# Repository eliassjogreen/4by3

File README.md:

<br/>

A 12 key mechanical keypad that can be used as a arrow-pad, function-pad, numpad or whatever else you can imagine that fits onto 12  keys.

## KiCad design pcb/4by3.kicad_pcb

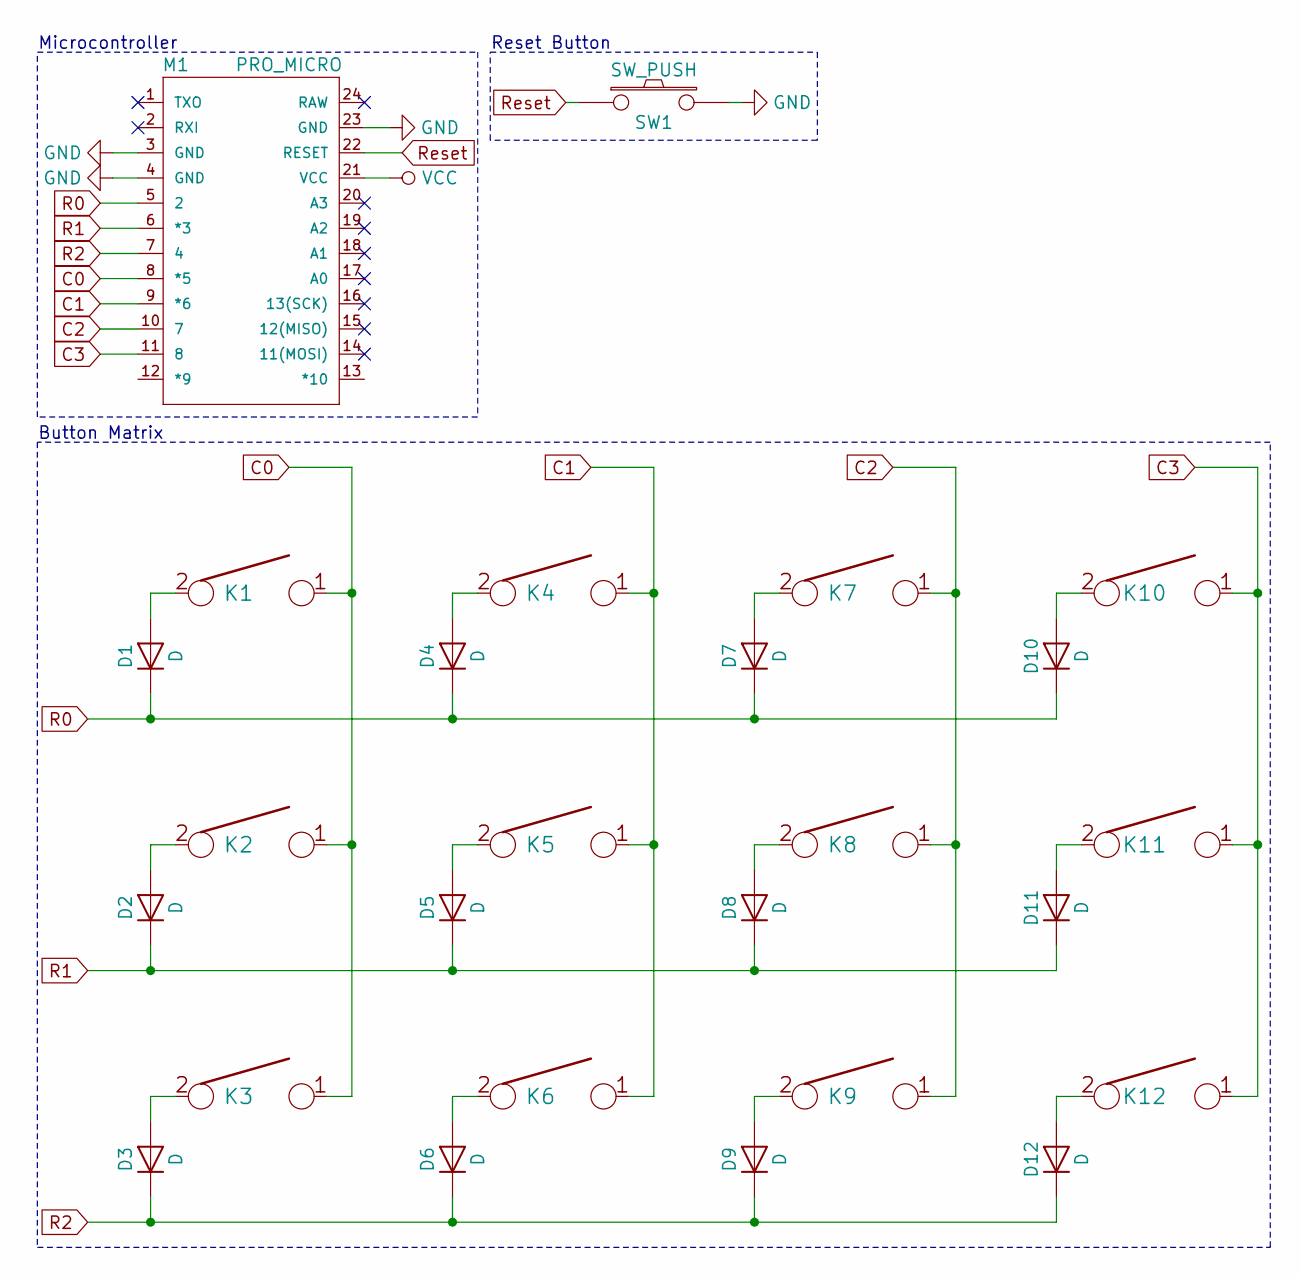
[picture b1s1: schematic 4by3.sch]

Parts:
D1, D2, D3, D4, D5, D6, D7, D8, D9, D10, D11, D12: D; DIODE
K1, K2, K3, K4, K5, K6, K7, K8, K9, K10, K11, K12: KEYSW; CHERRY_MX_PCB
M1: PRO_MICRO
SW1: SW_PUSH; RESET_BUTTON

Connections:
C0: K1.1, K2.1, K3.1, M1.8 (*5)
C1: K4.1, K5.1, K6.1, M1.9 (*6)
C2: K7.1, K8.1, K9.1, M1.10 (7)
C3: K10.1, K11.1, K12.1, M1.11 (8)
GND: M1.3 (GND), M1.4 (GND), M1.23 (GND), SW1.2
unnamed: D1.2 (A), K1.2
unnamed: D2.2 (A), K2.2
unnamed: D3.2 (A), K3.2
unnamed: D4.2 (A), K4.2
unnamed: D5.2 (A), K5.2
unnamed: D6.2 (A), K6.2
unnamed: D7.2 (A), K7.2
unnamed: D8.2 (A), K8.2
unnamed: D9.2 (A), K9.2
unnamed: D10.2 (A), K10.2
unnamed: D11.2 (A), K11.2
unnamed: D12.2 (A), K12.2
R0: D1.1 (K), D4.1 (K), D7.1 (K), D10.1 (K), M1.5 (2)
R1: D2.1 (K), D5.1 (K), D8.1 (K), D11.1 (K), M1.6 (*3)
R2: D3.1 (K), D6.1 (K), D9.1 (K), D12.1 (K), M1.7 (4)
Reset: M1.22 (RESET), SW1.1

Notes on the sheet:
Microcontroller
Reset Button
Button Matrix

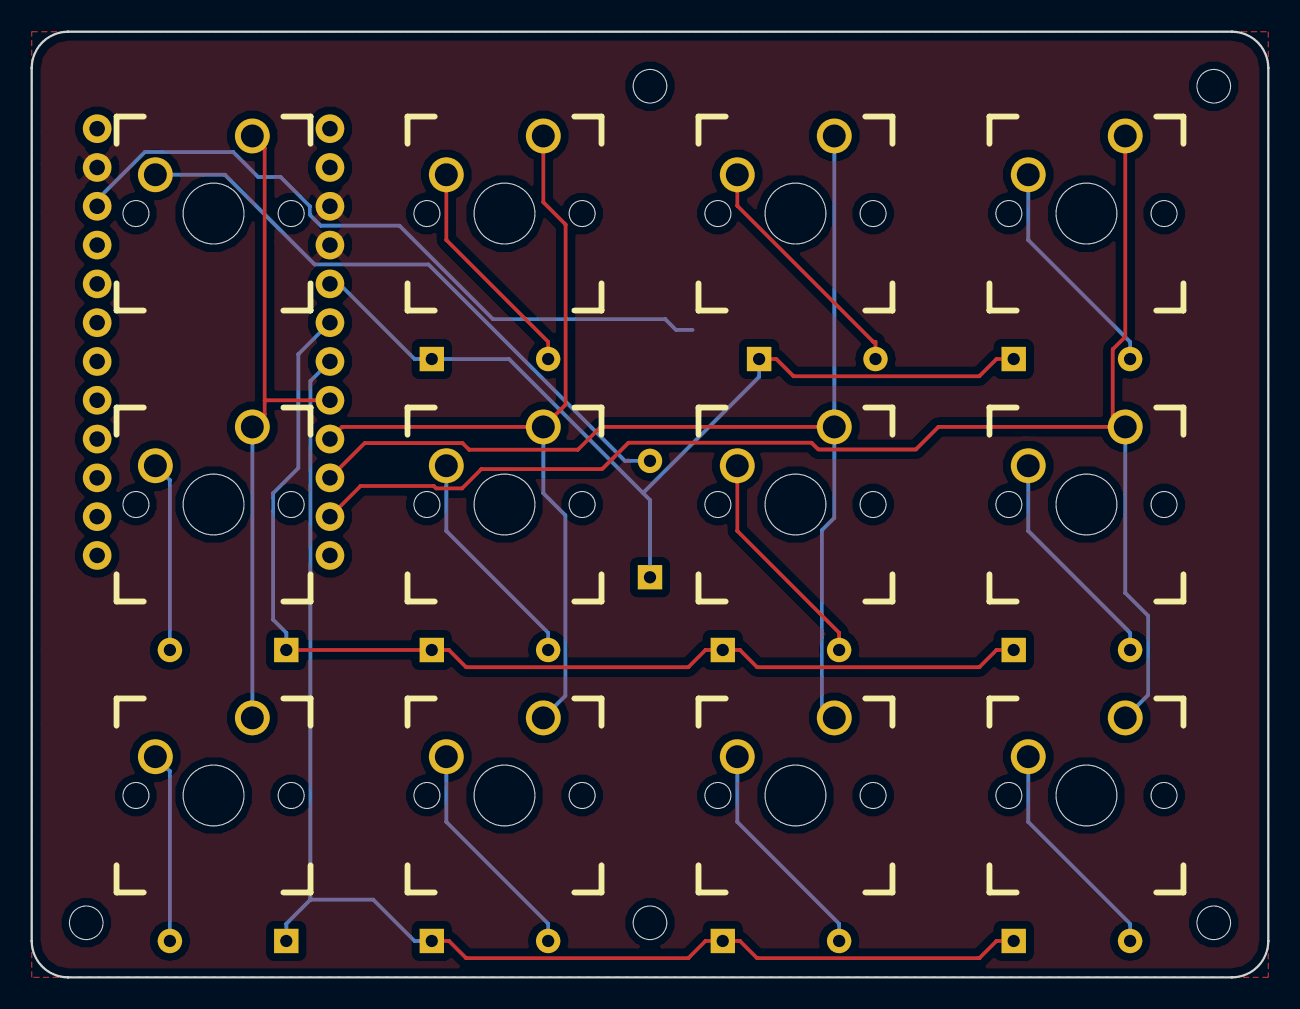
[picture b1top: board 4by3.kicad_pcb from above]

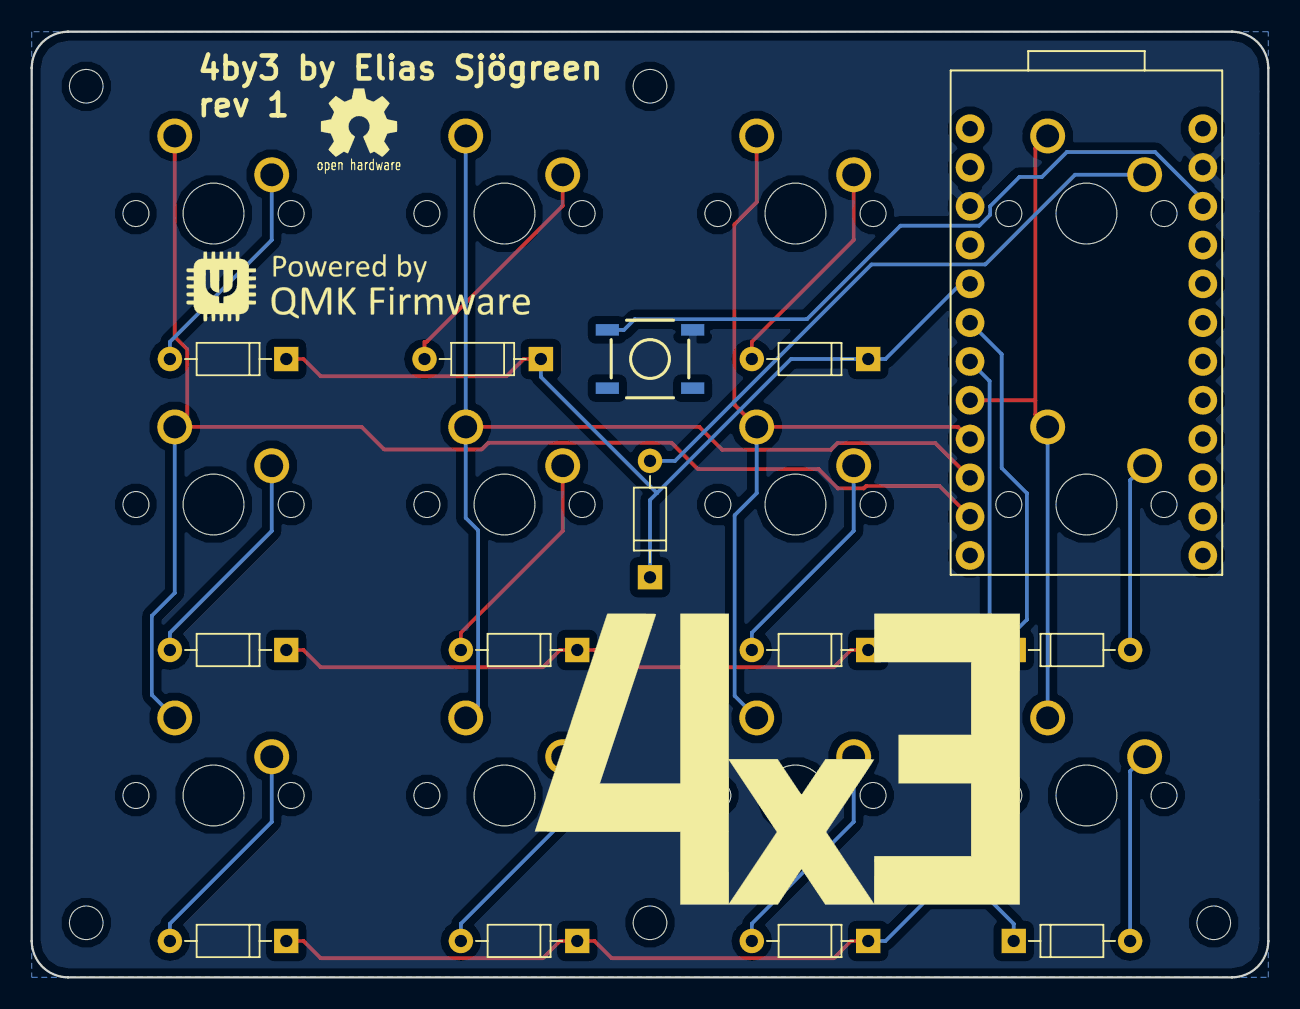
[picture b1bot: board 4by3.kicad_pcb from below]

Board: 2 copper layers, 81.0 x 61.9 mm, 33 parts (16 on the bottom side), 21 nets.

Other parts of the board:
>NAME: >VALUE; OSHW_LOGO
G: LOGO; QMK_BADGE
H1, H2, H4, H5: MOUNTING_HOLE
H3: MountingHole_2.2mm_M2

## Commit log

2019-08-15 Fixed pro micro pcb, created qmk firmware for the device
2019-08-15 Changed text on pcb and wrote README.md
2019-08-15 Added images, created a pretty library
2019-08-15 Added MIT license
2019-08-15 Added files for a plate case
2019-08-15 Added a few keymaps, updated readme
2019-08-15 Moved firmware to qmk/qmk_firmware and modified the README.md
